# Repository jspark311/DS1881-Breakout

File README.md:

# DS1881-Breakout

A breakout board for the Dallas/Maxim i2c logarithmic potentiometer.

#### [Hackaday.io Page](https://hackaday.io/project/167234-ds1881-breakout)

#### [Order from Tindie](https://www.tindie.com/products/17867/)

#### [Arduino driver](https://github.com/jspark311/Arduino-DS1881)

------------------------

### What is in this repository:

**./doc**:  Location for documentation

**./KiCAD**:  Hardware design files

------------------------

Front | Back
:-------:|:------:
  |

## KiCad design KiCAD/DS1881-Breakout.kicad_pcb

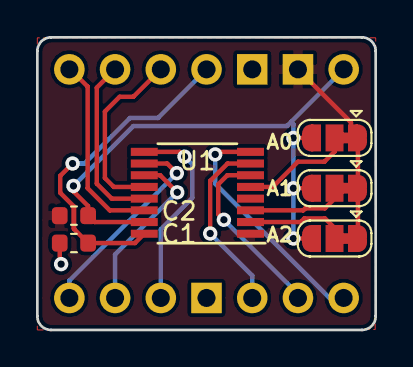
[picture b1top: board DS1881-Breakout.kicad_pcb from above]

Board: 2 copper layers, 18.8 x 16.3 mm, 8 parts (0 on the bottom side), 16 nets.

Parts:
C1, C2: 1uF; C_0603_1608Metric
J1, J2: Conn_01x07_Male; PinHeader_1x07_P2.54mm_Vertical
J3, J4, J5: Conn_01x03_Male; SolderJumper-3_P1.3mm_Bridged12_RoundedPad1.0x1.5mm
U1: DS1881E-050+; TSSOP-16_4.4x5mm_P0.65mm

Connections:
/A0: J3.2, U1.5
/A1: J4.2, U1.3
/A2: J5.2, U1.2
/ANAGND: C1.2, J1.4, J2.3
/ANAVcc: C1.1, J2.4, U1.16
/GND: C2.2, J2.2, J3.1, J4.1, J5.1, U1.1
/H0: J1.1, U1.8
/H1: J1.7, U1.10
/L0: J1.3, U1.7
/L1: J1.5, U1.9
/SCL: J2.7, U1.14
/SDA: J2.6, U1.13
/Vcc: C2.1, J2.1, J3.3, J4.3, J5.3, U1.15
/W0: J1.2, U1.6
/W1: J1.6, U1.11
/~CE: J2.5, U1.12

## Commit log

2019-08-21 Adding hardware, and updating README.
2019-08-21 Updating README.
2019-08-21 Adding arduino boilerplate and an unported driver.
2019-08-27 Arduino driver almost works.
2019-11-25 Improving driver for more reliable error reporting.
2019-11-26 Fixing some mistakes in the driver. Improving example.
2019-11-30 Implemented (un)serialize. Consolidated bools into flags. Updated example sketch.
2019-11-30 Bus is now passed in as parameter it init().
2019-12-04 Documentation.
2019-12-04 Fixes for linux build.
2019-12-05 Fixed a bug in unserialize().
2019-12-08 Now using StringBuilder for debugging output. Isolated by preprocessor flag.
2019-12-18 Fix for silly mistake in debug print fxn.
2020-02-22 Arduino driver is now in the Library manager.
